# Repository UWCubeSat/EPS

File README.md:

# [Electrical Power System](https://online.huskysatellitelab.com/wiki/index.php/Electrical_Power_System)

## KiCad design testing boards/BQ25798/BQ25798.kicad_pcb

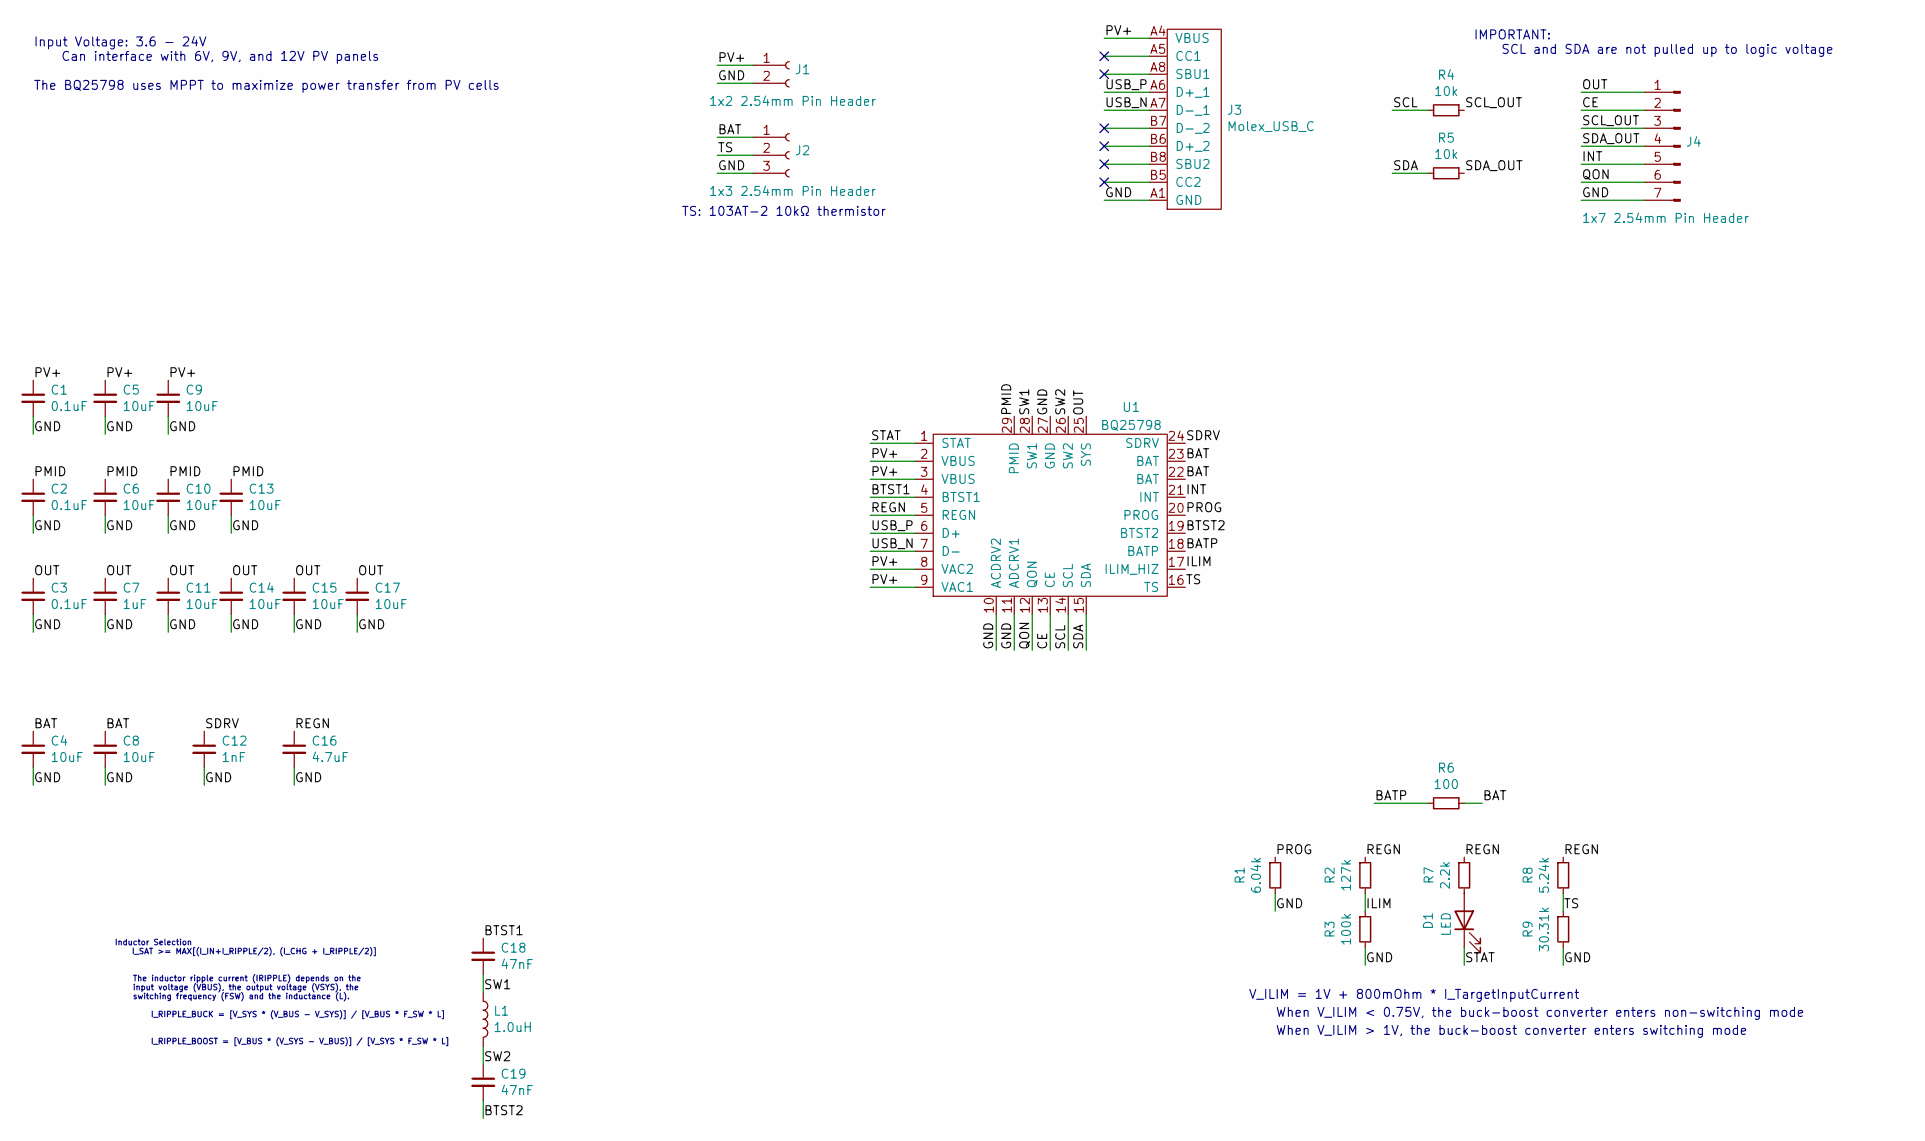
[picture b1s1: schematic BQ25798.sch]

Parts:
C1, C2, C3: 0.1uF; C_0603_1608Metric
C4, C5, C6, C8, C9, C10, C11, C13, C14, C15, C17: 10uF; C_0603_1608Metric
C7: 1uF; C_0603_1608Metric
C12: 1nF; C_0603_1608Metric
C16: 4.7uF; C_0603_1608Metric
C18, C19: 47nF; C_0603_1608Metric
D1: LED; LED_0402_1005Metric
J1: 1x2 2.54mm Pin Header; PinHeader_1x02_P2.54mm_Vertical
J2: 1x3 2.54mm Pin Header; PinHeader_1x03_P2.54mm_Vertical
J3: Molex_USB_C; USB-C
J4: 1x7 2.54mm Pin Header; PinHeader_1x07_P2.54mm_Vertical
L1: 1.0uH; L_0805_2012Metric
R1: 6.04k; R_0402_1005Metric
R2: 127k; R_0402_1005Metric
R3: 100k; R_0402_1005Metric
R4, R5: 10k; R_0402_1005Metric
R6: 100; R_0402_1005Metric
R7: 2.2k; R_0402_1005Metric
R8: 5.24k; R_0402_1005Metric
R9: 30.31k; R_0402_1005Metric
U1: BQ25798

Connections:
/BAT: C4.1, C8.1, J2.1, R6.1, U1.22 (BAT), U1.23 (BAT)
/BATP: R6.2, U1.18 (BATP)
/BTST1: C18.1, U1.4 (BTST1)
/BTST2: C19.2, U1.19 (BTST2)
/CE: J4.2, U1.13 (CE)
/GND: C1.2, C2.2, C3.2, C4.2, C5.2, C6.2, C7.2, C8.2, C9.2, C10.2, C11.2, C12.2, C13.2, C14.2, C15.2, C16.2, C17.2, J1.2, J2.3, J3.A1 (GND), J4.7, R1.2, R3.2, R9.2, U1.10 (ACDRV2), U1.11 (ADCRV1), U1.27 (GND)
/ILIM: R2.2, R3.1, U1.17 (ILIM_HIZ)
/INT: J4.5, U1.21 (INT)
/OUT: C3.1, C7.1, C11.1, C14.1, C15.1, C17.1, J4.1, U1.25 (SYS)
/PMID: C2.1, C6.1, C10.1, C13.1, U1.29 (PMID)
/PROG: R1.1, U1.20 (PROG)
/PV+: C1.1, C5.1, C9.1, J1.1, J3.A4 (VBUS), U1.2 (VBUS), U1.3 (VBUS), U1.8 (VAC2), U1.9 (VAC1)
/QON: J4.6, U1.12 (QON)
/REGN: C16.1, R2.1, R7.1, R8.1, U1.5 (REGN)
/SCL: R4.2, U1.14 (SCL)
/SCL_OUT: J4.3, R4.1
/SDA: R5.2, U1.15 (SDA)
/SDA_OUT: J4.4, R5.1
/SDRV: C12.1, U1.24 (SDRV)
/STAT: D1.1 (K), U1.1 (STAT)
/SW1: C18.2, L1.1, U1.28 (SW1)
/SW2: C19.1, L1.2, U1.26 (SW2)
/TS: J2.2, R8.2, R9.1, U1.16 (TS)
/USB_N: J3.A7 (D-_1), U1.7 (D-)
/USB_P: J3.A6 (D+_1), U1.6 (D+)
unnamed: D1.2 (A), R7.2

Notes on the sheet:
Input Voltage: 3.6 - 24V Can interface with 6V, 9V, and 12V PV panels The BQ25798 uses MPPT to maximize power transfer from PV cells
Inductor Selection I_SAT >= MAX[(I_IN+I_RIPPLE/2), (I_CHG + I_RIPPLE/2)]
I_RIPPLE_BUCK = [V_SYS * (V_BUS - V_SYS)] / [V_BUS * F_SW * L]
I_RIPPLE_BOOST = [V_BUS * (V_SYS - V_BUS)] / [V_SYS * F_SW * L]
The inductor ripple current (IRIPPLE) depends on the input voltage (VBUS), the output voltage (VSYS), the switching frequency (FSW) and the inductance (L).
V_ILIM = 1V + 800mOhm * I_TargetInputCurrent
When V_ILIM < 0.75V, the buck-boost converter enters non-switching mode
When V_ILIM > 1V, the buck-boost converter enters switching mode
IMPORTANT: SCL and SDA are not pulled up to logic voltage
TS: 103AT-2 10kΩ thermistor

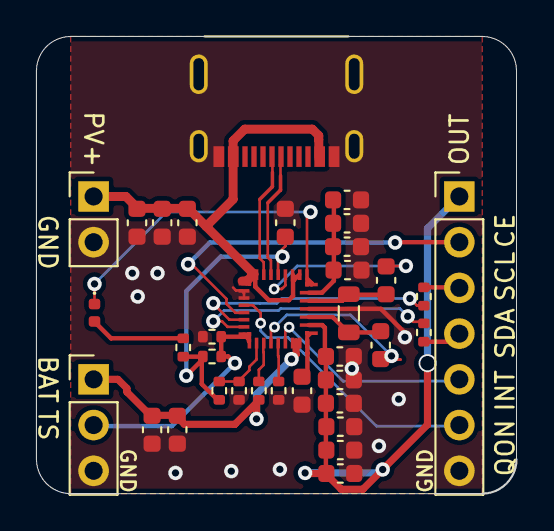
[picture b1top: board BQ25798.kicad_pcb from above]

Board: 2 copper layers, 26.7 x 25.4 mm, 35 parts (0 on the bottom side), 26 nets.

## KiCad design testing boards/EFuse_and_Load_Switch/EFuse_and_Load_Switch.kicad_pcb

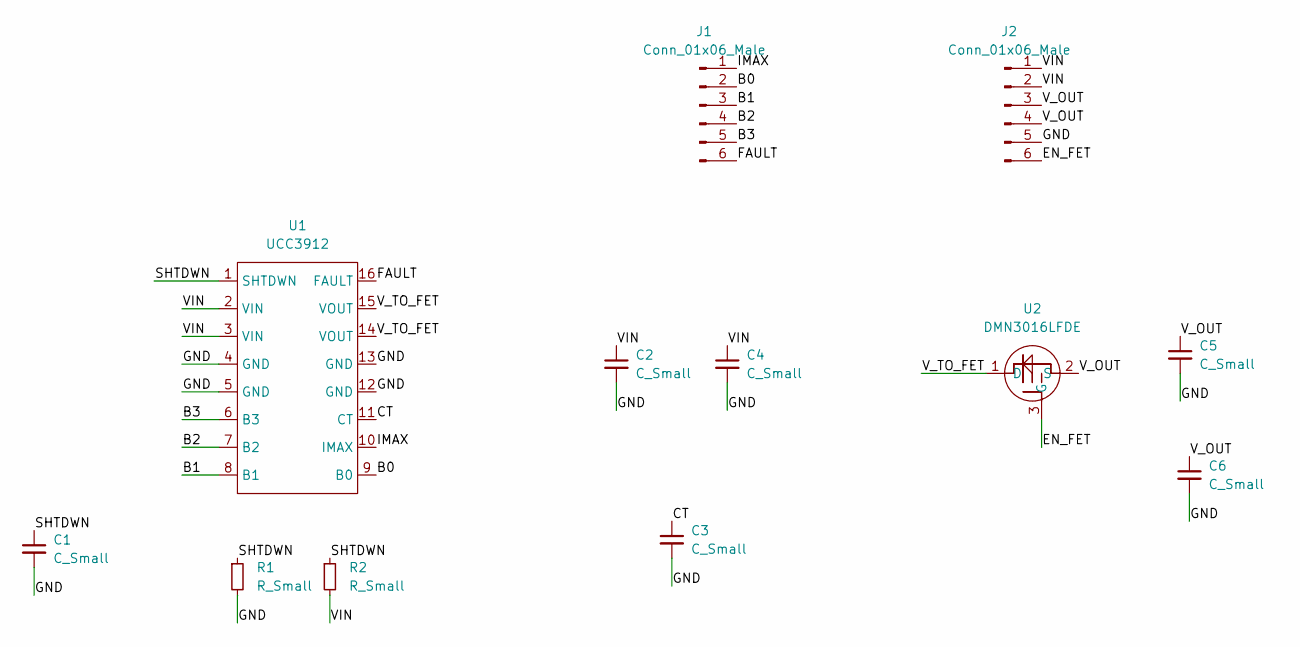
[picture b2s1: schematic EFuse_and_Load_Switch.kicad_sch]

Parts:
C1, C2, C3, C4, C5, C6: C_Small; C_0603_1608Metric
J1, J2: Conn_01x06_Male; PinHeader_1x06_P2.54mm_Vertical
R1, R2: R_Small; R_0402_1005Metric
U1: UCC3912
U2: DMN3016LFDE; U-DFN2020-6

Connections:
/B0: J1.2, U1.9 (B0)
/B1: J1.3, U1.8 (B1)
/B2: J1.4, U1.7 (B2)
/B3: J1.5, U1.6 (B3)
/CT: C3.1, U1.11 (CT)
/EN_FET: J2.6, U2.3 (G)
/FAULT: J1.6, U1.16 (FAULT)
/GND: C1.2, C2.2, C3.2, C4.2, C5.2, C6.2, J2.5, R1.2, U1.4 (GND), U1.5 (GND), U1.12 (GND), U1.13 (GND)
/IMAX: J1.1, U1.10 (IMAX)
/SHTDWN: C1.1, R1.1, R2.1, U1.1 (SHTDWN)
/VIN: C2.1, C4.1, J2.1, J2.2, R2.2, U1.2 (VIN), U1.3 (VIN)
/V_OUT: C5.1, C6.1, J2.3, J2.4, U2.2 (S)
/V_TO_FET: U1.14 (VOUT), U1.15 (VOUT), U2.1 (D)

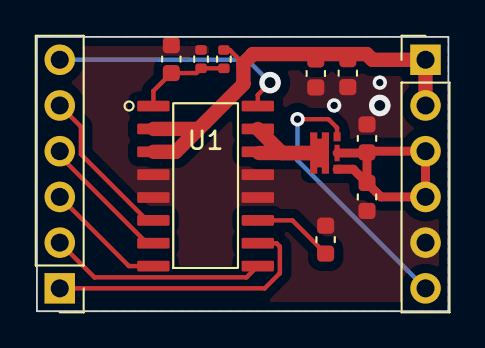
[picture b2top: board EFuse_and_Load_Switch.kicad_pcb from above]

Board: 2 copper layers, 22.9 x 15.2 mm, 12 parts (0 on the bottom side), 13 nets.

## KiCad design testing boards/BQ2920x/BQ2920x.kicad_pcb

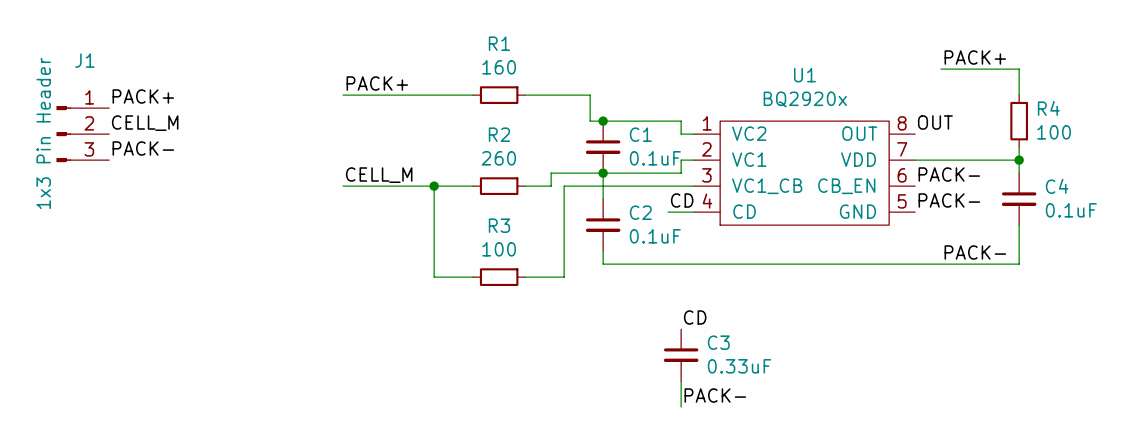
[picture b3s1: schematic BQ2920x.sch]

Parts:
C1, C2, C4: 0.1uF; C_0603_1608Metric
C3: 0.33uF; C_0603_1608Metric
J1: 1x3 Pin Header; PinHeader_1x03_P2.54mm_Vertical
R1: 160; R_0402_1005Metric
R2: 260; R_0402_1005Metric
R3, R4: 100; R_0402_1005Metric
U1: BQ2920x

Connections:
/CD: C3.1, U1.4 (CD)
/CELL_M: J1.2, R2.2, R3.2
/OUT: U1.8 (OUT)
/PACK+: J1.1, R1.2, R4.2
/PACK-: C2.2, C3.2, C4.2, J1.3, U1.5 (GND), U1.6 (CB_EN)
unnamed: C1.1, R1.1, U1.1 (VC2)
unnamed: C1.2, C2.1, R2.1, U1.2 (VC1)
unnamed: C4.1, R4.1, U1.7 (VDD)
unnamed: R3.1, U1.3 (VC1_CB)

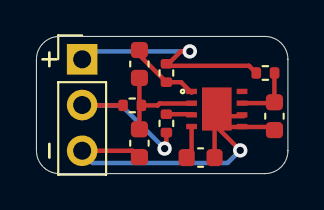
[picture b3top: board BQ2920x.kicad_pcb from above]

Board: 2 copper layers, 14.0 x 7.6 mm, 10 parts (0 on the bottom side), 8 nets.

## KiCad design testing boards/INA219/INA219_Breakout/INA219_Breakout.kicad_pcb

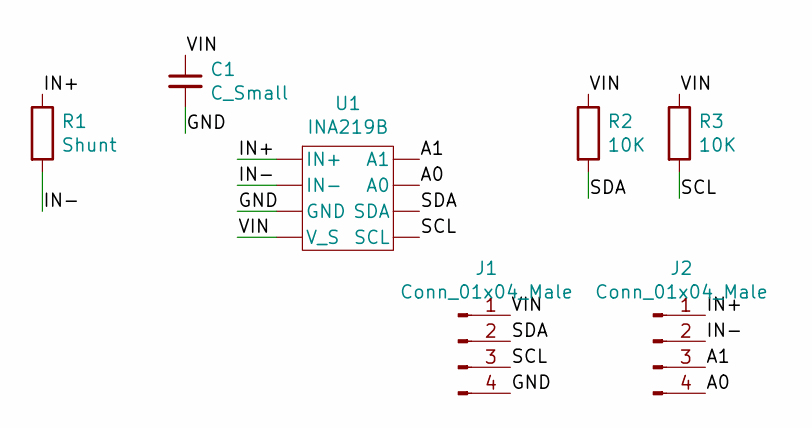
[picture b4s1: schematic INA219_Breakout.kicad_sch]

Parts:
C1: C_Small; C_0603_1608Metric
J1, J2: Conn_01x04_Male; PinHeader_1x04_P2.54mm_Vertical
R1: Shunt; R_2512_6332Metric
R2, R3: 10K; R_0402_1005Metric
U1: INA219B; SOT-23-8

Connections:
/A0: J2.4, U1.7 (A0)
/A1: J2.3, U1.8 (A1)
/GND: C1.2, J1.4, U1.3 (GND)
/IN+: J2.1, R1.1, U1.1 (IN+)
/IN-: J2.2, R1.2, U1.2 (IN-)
/SCL: J1.3, R3.2, U1.5 (SCL)
/SDA: J1.2, R2.2, U1.6 (SDA)
/VIN: C1.1, J1.1, R2.1, R3.1, U1.4 (V_S)

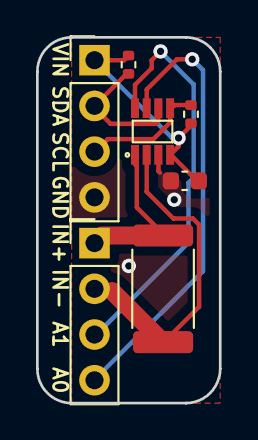
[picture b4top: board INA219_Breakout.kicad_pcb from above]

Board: 2 copper layers, 10.2 x 20.3 mm, 7 parts (0 on the bottom side), 8 nets.

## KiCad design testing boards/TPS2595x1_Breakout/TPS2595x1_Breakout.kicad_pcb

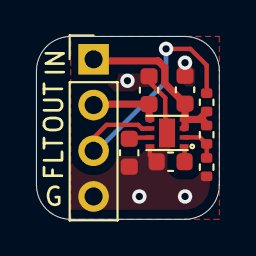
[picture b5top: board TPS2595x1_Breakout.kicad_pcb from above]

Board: 2 copper layers, 10.2 x 10.2 mm, 9 parts (0 on the bottom side), 7 nets.

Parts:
C1, C2, C3, C4: 1uF; C_0603_1608Metric
J1: Pin Header; PinHeader_1x04_P2.54mm_Vertical
R1, R2, R3: 10K; R_0402_1005Metric
U1: TPS2595x1

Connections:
/EN: R1.2, R2.1, U1.2
/FLT: J1.3, R3.2, U1.6
/GND: C1.2, C2.2, C3.2, C4.2, J1.4, R2.2, U1.8
/ILM: C2.1, U1.7
/IN: C3.1, J1.1, R1.1, R3.1, U1.3, U1.4
/OUT: C4.1, J1.2, U1.5
/dVdt: C1.1, U1.1

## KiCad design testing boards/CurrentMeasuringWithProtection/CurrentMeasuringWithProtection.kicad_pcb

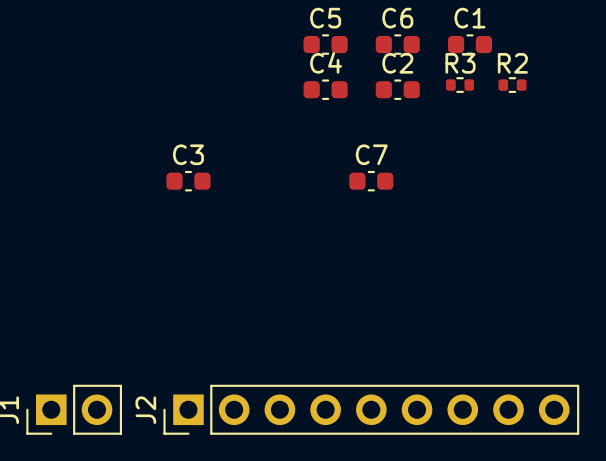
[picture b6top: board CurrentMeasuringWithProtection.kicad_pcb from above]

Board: 2 copper layers, 11 parts (0 on the bottom side), 6 nets, no tracks yet.

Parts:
C1, C2, C3, C4, C5, C6, C7: C_Small; C_0603_1608Metric
J1: Conn_01x02_Male; PinHeader_1x02_P2.54mm_Vertical
J2: Conn_01x09_Male; PinHeader_1x09_P2.54mm_Vertical
R2, R3: R_Small; R_0402_1005Metric

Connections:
/3V3: J2.1, R2.1, R3.1
/GND: C1.2, C2.2, C3.2, C4.2, C5.2, C6.2, C7.2, J2.9
/IN+: C1.1, C2.1, J1.1
/SCL: J2.5, R3.2
/SDA: J2.4, R2.2
/V_OUT: C6.1, C7.1, J1.2

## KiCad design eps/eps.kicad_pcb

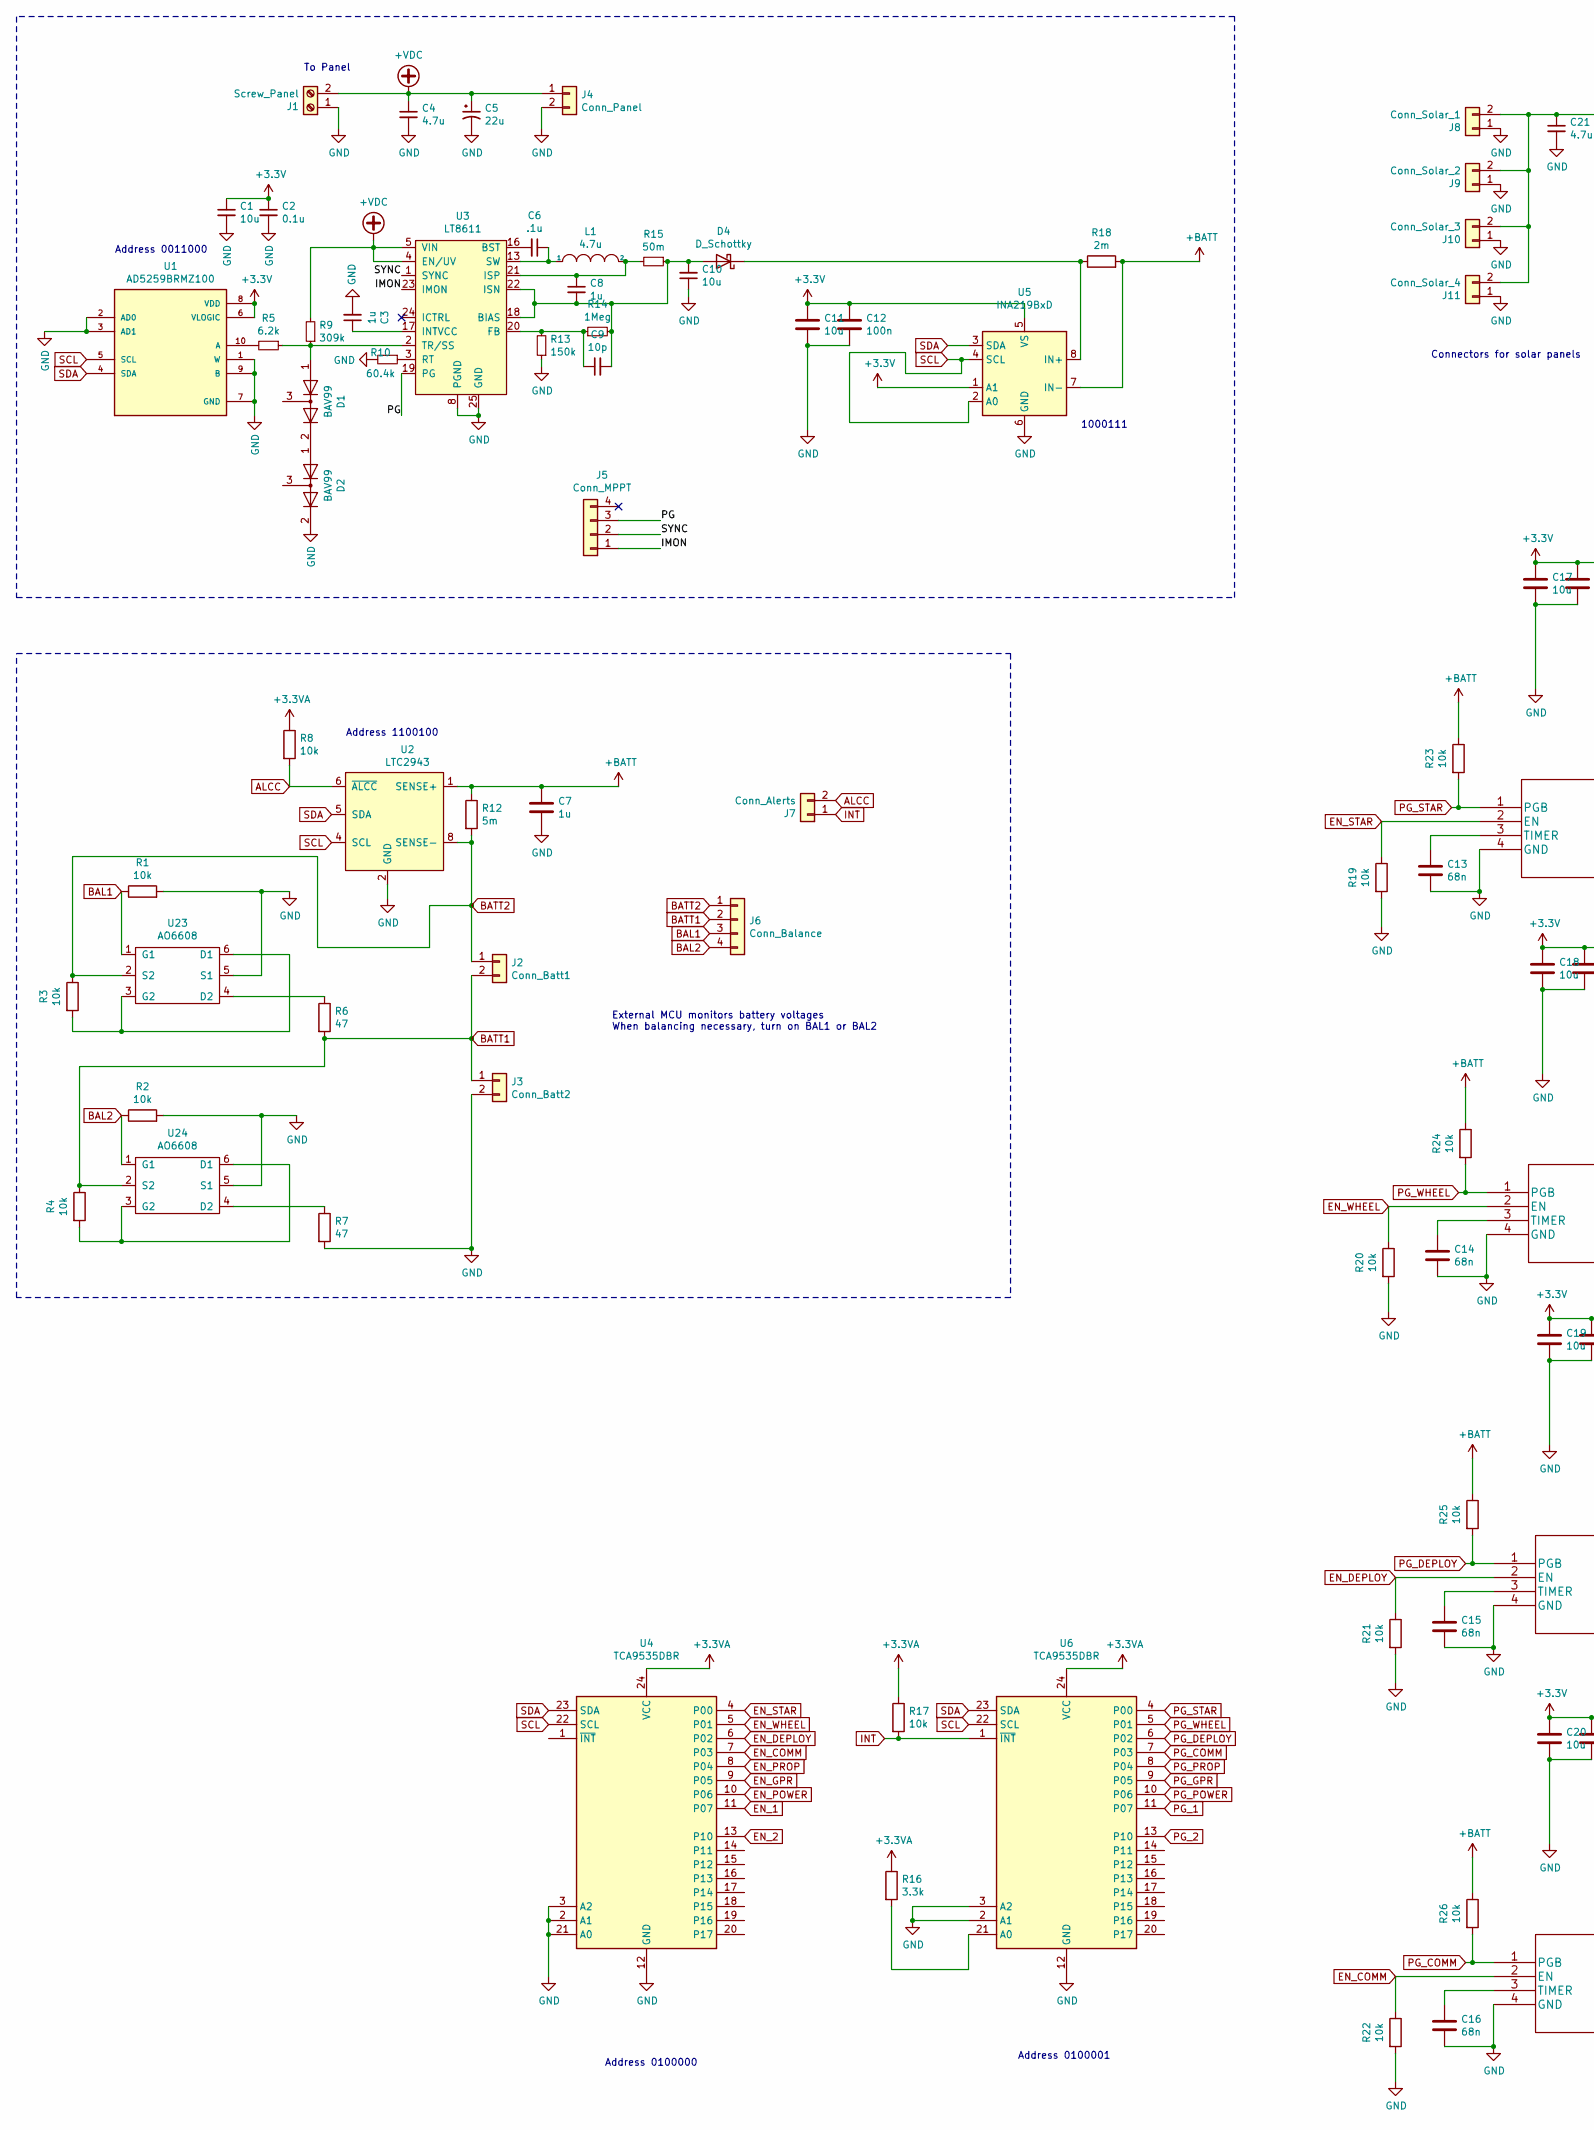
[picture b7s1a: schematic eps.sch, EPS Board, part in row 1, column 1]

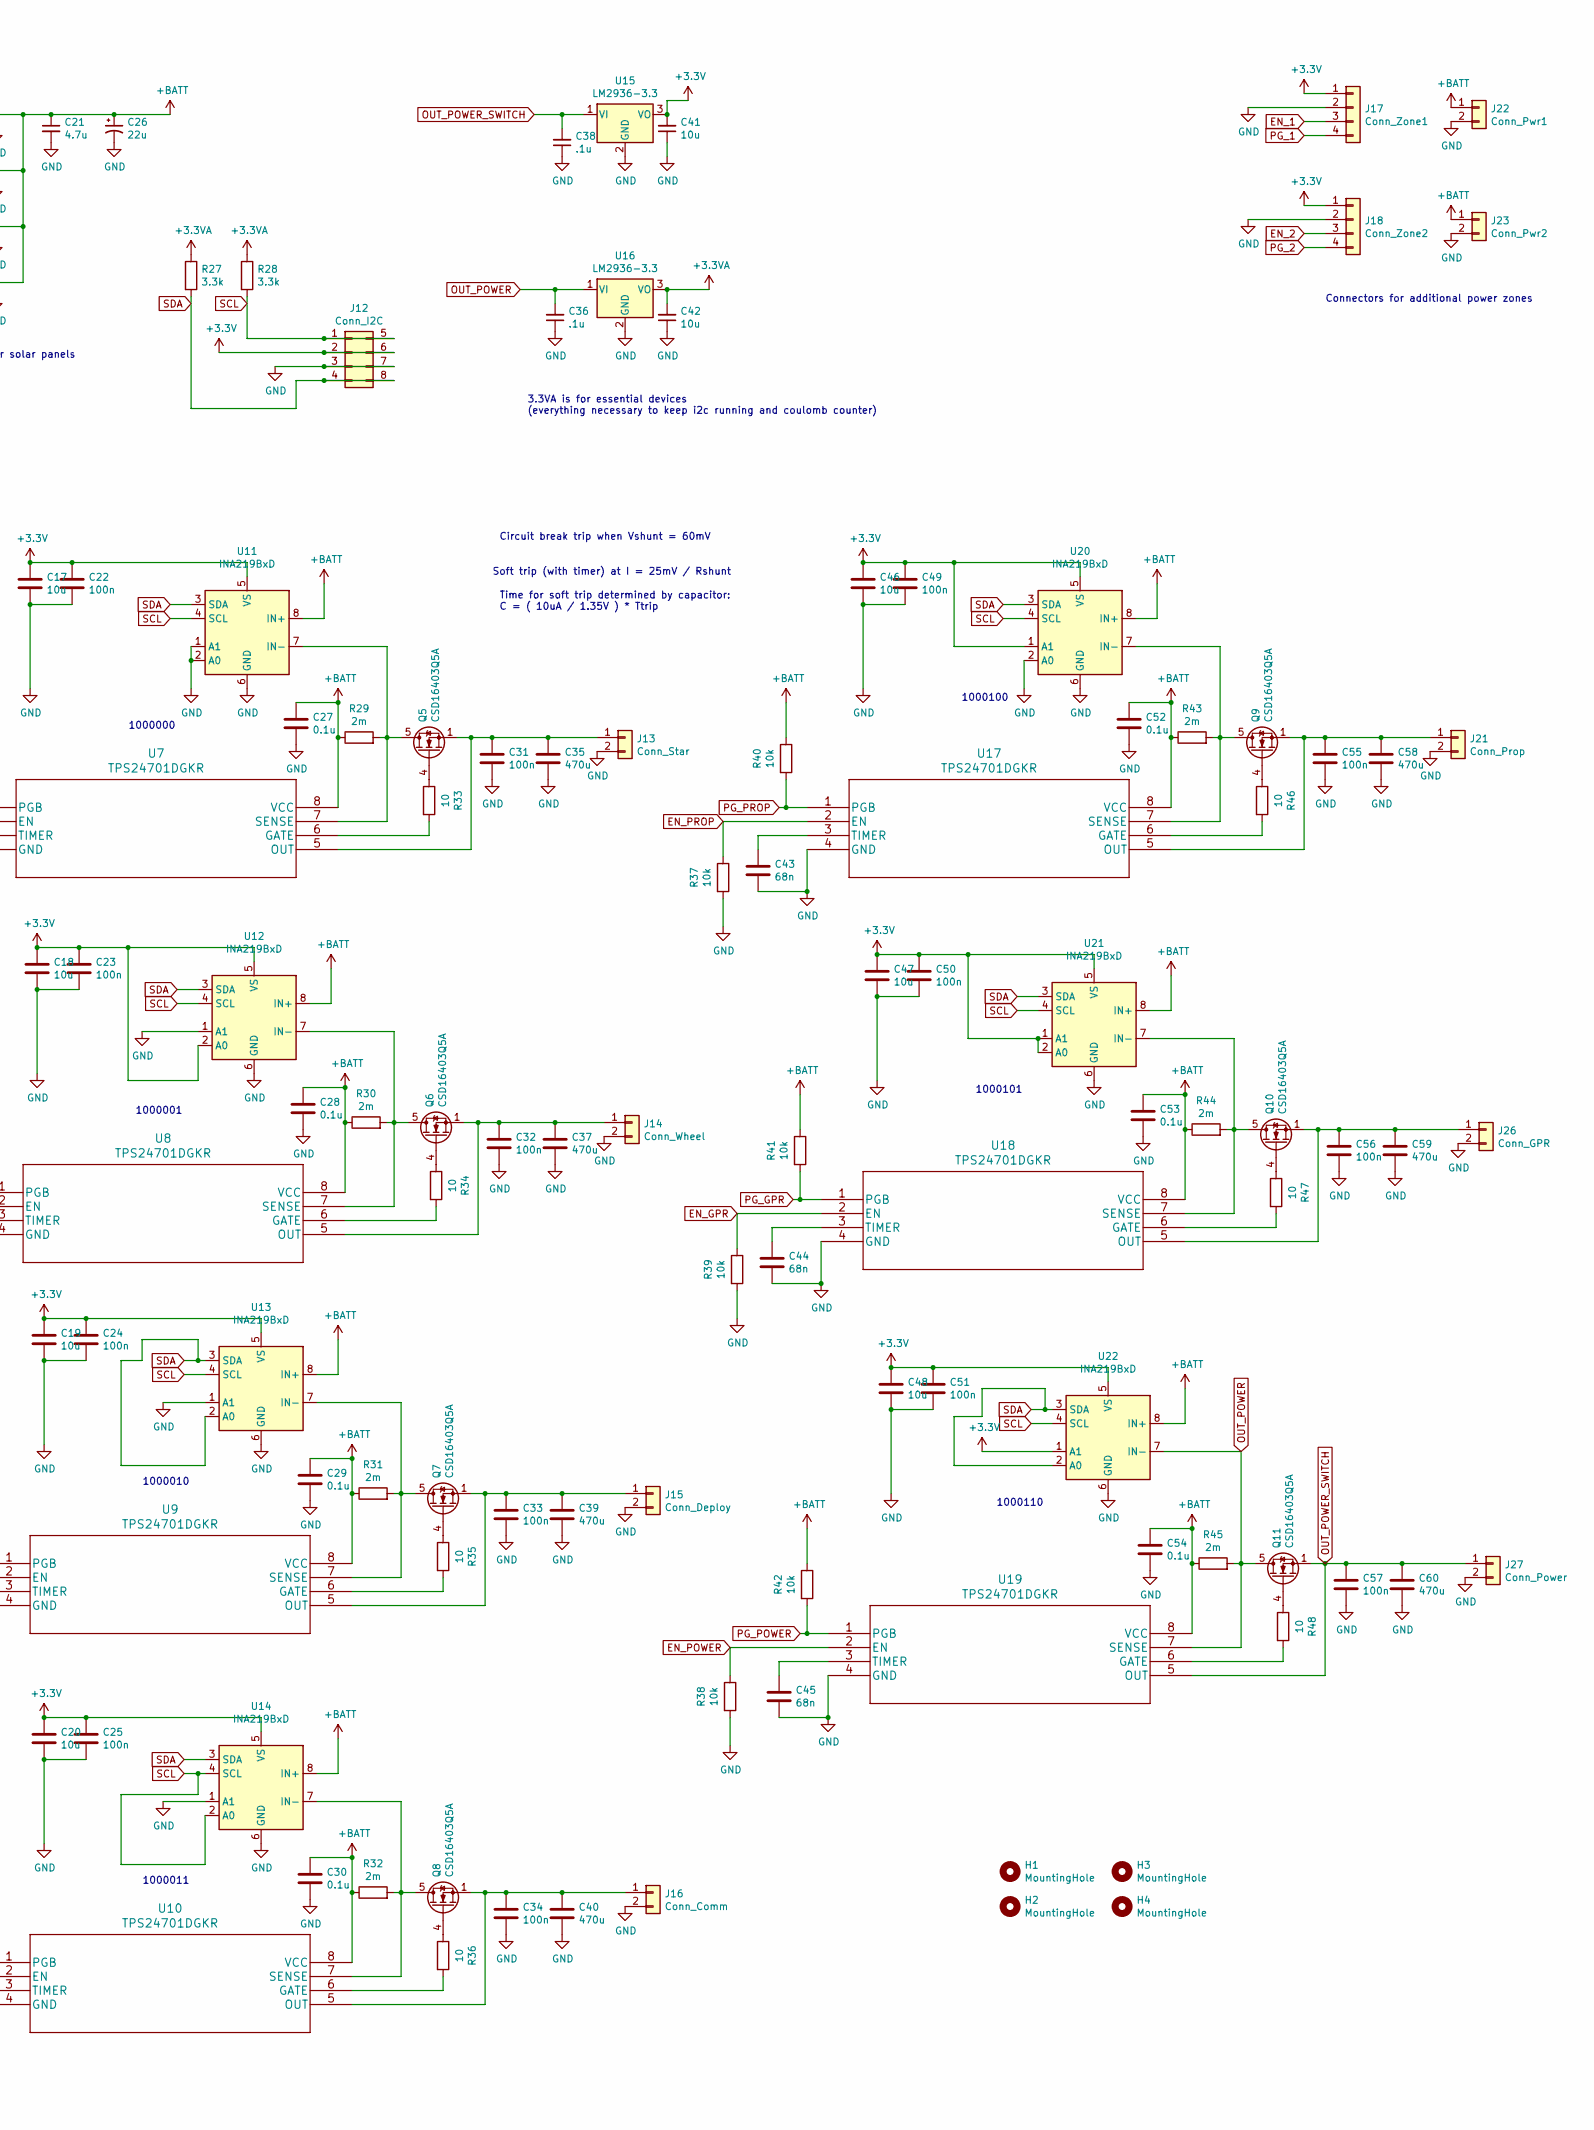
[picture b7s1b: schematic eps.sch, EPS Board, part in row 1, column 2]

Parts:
C1, C10, C11, C17, C18, C19, C20, C41, C42, C46, C47, C48: 10u; C_0805_2012Metric_Pad1.18x1.45mm_HandSolder; Part C15850
C2, C27, C28, C29, C30, C52, C53, C54: 0.1u; C_0805_2012Metric_Pad1.18x1.45mm_HandSolder; Part C49678
C3, C7, C8: 1u; C_0805_2012Metric_Pad1.18x1.45mm_HandSolder; Part C28323
C4, C21: 4.7u; C_0805_2012Metric_Pad1.18x1.45mm_HandSolder; Part C1779
C5, C26: 22u; CP_Radial_D6.3mm_P2.50mm
C6, C36, C38: .1u; C_0805_2012Metric_Pad1.18x1.45mm_HandSolder; Part C49678
C9: 10p; C_0805_2012Metric_Pad1.18x1.45mm_HandSolder; Part C1785
C12, C22, C23, C24, C25, C31, C32, C33, C34, C49, C50, C51, C55, C56, C57: 100n; C_0805_2012Metric_Pad1.18x1.45mm_HandSolder; Part C49678
C13, C14, C15, C16, C43, C44, C45: 68n; C_0805_2012Metric_Pad1.18x1.45mm_HandSolder; Part C1756
C35, C37, C39, C40, C58, C59, C60: 470u; CP_Radial_D8.0mm_P3.50mm
D1, D2: BAV99; SOT-23; Part C2500
D4: D_Schottky; D_SOD-128
H1, H2, H3, H4: MountingHole; MountingHole_2.7mm_M2.5_Pad_Via; Part x
J1: Screw_Panel; TerminalBlock_Phoenix_PT-1,5-2-5.0-H_1x02_P5.00mm_Horizontal
J2: Conn_Batt1; Molex_Micro-Fit_3.0_43045-0212_2x01_P3.00mm_Vertical
J3: Conn_Batt2; Molex_Micro-Fit_3.0_43045-0212_2x01_P3.00mm_Vertical
J4: Conn_Panel; JST_XH_B2B-XH-AM_1x02_P2.50mm_Vertical
J5: Conn_MPPT; JST_XH_B4B-XH-AM_1x04_P2.50mm_Vertical
J6: Conn_Balance; JST_XH_B4B-XH-AM_1x04_P2.50mm_Vertical
J7: Conn_Alerts; JST_XH_B2B-XH-AM_1x02_P2.50mm_Vertical
J8: Conn_Solar_1; JST_XH_B2B-XH-AM_1x02_P2.50mm_Vertical
J9: Conn_Solar_2; JST_XH_B2B-XH-AM_1x02_P2.50mm_Vertical
J10: Conn_Solar_3; JST_XH_B2B-XH-AM_1x02_P2.50mm_Vertical
J11: Conn_Solar_4; JST_XH_B2B-XH-AM_1x02_P2.50mm_Vertical
J12: Conn_I2C; JST_PHD_B8B-PHDSS_2x04_P2.00mm_Vertical
J13: Conn_Star; Molex_Micro-Fit_3.0_43045-0212_2x01_P3.00mm_Vertical
J14: Conn_Wheel; Molex_Micro-Fit_3.0_43045-0212_2x01_P3.00mm_Vertical
J15: Conn_Deploy; Molex_Micro-Fit_3.0_43045-0212_2x01_P3.00mm_Vertical
J16: Conn_Comm; Molex_Micro-Fit_3.0_43045-0212_2x01_P3.00mm_Vertical
J17: Conn_Zone1; JST_XH_B4B-XH-AM_1x04_P2.50mm_Vertical
J18: Conn_Zone2; JST_XH_B4B-XH-AM_1x04_P2.50mm_Vertical
J21: Conn_Prop; Molex_Micro-Fit_3.0_43045-0212_2x01_P3.00mm_Vertical
J22: Conn_Pwr1; Molex_Micro-Fit_3.0_43045-0212_2x01_P3.00mm_Vertical
J23: Conn_Pwr2; Molex_Micro-Fit_3.0_43045-0212_2x01_P3.00mm_Vertical
J26: Conn_GPR; Molex_Micro-Fit_3.0_43045-0212_2x01_P3.00mm_Vertical
J27: Conn_Power; Molex_Micro-Fit_3.0_43045-0212_2x01_P3.00mm_Vertical
L1: 4.7u; BWVS00606045
Q5, Q6, Q7, Q8, Q9, Q10, Q11: CSD16403Q5A; TDSON-8-1
R1, R2, R3, R4, R8, R17, R19, R20, R21, R22, R23, R24, R25, R26, R37, R38, R39, R40, R41, R42: 10k; R_0805_2012Metric_Pad1.20x1.40mm_HandSolder; Part C17414
R5: 6.2k; R_0805_2012Metric_Pad1.20x1.40mm_HandSolder; Part C17767
R6, R7: 47; R_2512_6332Metric_Pad1.40x3.35mm_HandSolder
R9: 309k; R_0805_2012Metric_Pad1.20x1.40mm_HandSolder
R10: 60.4k; R_0805_2012Metric_Pad1.20x1.40mm_HandSolder
R12: 5m; R_2512_6332Metric_Pad1.40x3.35mm_HandSolder
R13: 150k; R_0805_2012Metric_Pad1.20x1.40mm_HandSolder; Part C17470
R14: 1Meg; R_0805_2012Metric_Pad1.20x1.40mm_HandSolder; Part C17514
R15: 50m; R_2512_6332Metric_Pad1.40x3.35mm_HandSolder
R16, R27, R28: 3.3k; R_0805_2012Metric_Pad1.20x1.40mm_HandSolder; Part C26010
R18, R29, R30, R31, R32, R43, R44, R45: 2m; R_0805_2012Metric_Pad1.20x1.40mm_HandSolder
R33, R34, R35, R36, R46, R47, R48: 10; R_0805_2012Metric_Pad1.20x1.40mm_HandSolder; Part C17415
U1: AD5259BRMZ100; SOP50P490X95-10N
U2: LTC2943; DFN-8-1EP_3x3mm_P0.5mm_EP1.66x2.38mm
U3: LT8611; 24-QFN_3x5
U4, U6: TCA9535DBR; SSOP-24_5.3x8.2mm_P0.65mm
U5, U11, U12, U13, U14, U20, U21, U22: INA219BxD; SOIC-8_3.9x4.9mm_P1.27mm
U7, U8, U9, U10, U17, U18, U19: TPS24701DGKR
U15, U16: LM2936-3.3; SOT-223-3_TabPin2
U23, U24: AO6608; SOT-23-6_Handsoldering

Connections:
+3.3VA: C42.2, R8.1, R16.1, R17.1, R27.1, R28.1, U4.24 (VCC), U6.24 (VCC), U16.3 (VO)
+3V3: C1.1, C2.1, C11.1, C12.1, C17.1, C18.1, C19.1, C20.1, C22.1, C23.1, C24.1, C25.1, C41.2, C46.1, C47.1, C48.1, C49.1, C50.1, C51.1, J12.2, J12.6, J17.1, J18.1, U1.6 (VLOGIC), U1.8 (VDD), U5.1 (A1), U5.5 (VS), U11.5 (VS), U12.2 (A0), U12.5 (VS), U13.5 (VS), U14.5 (VS), U15.3 (VO), U20.1 (A1), U20.5 (VS), U21.1 (A1), U21.2 (A0), U21.5 (VS), U22.1 (A1), U22.5 (VS)
+BATT: C7.1, C21.1, C26.1, C27.1, C28.1, C29.1, C30.1, C52.1, C53.1, C54.1, J8.2, J9.2, J10.2, J11.2, J22.1, J23.1, R12.1, R18.2, R23.1, R24.1, R25.1, R26.1, R29.1, R30.1, R31.1, R32.1, R40.1, R41.1, R42.1, R43.1, R44.1, R45.1, U2.1 (SENSE+), U5.7 (IN-), U7.8 (VCC), U8.8 (VCC), U9.8 (VCC), U10.8 (VCC), U11.8 (IN+), U12.8 (IN+), U13.8 (IN+), U14.8 (IN+), U17.8 (VCC), U18.8 (VCC), U19.8 (VCC), U20.8 (IN+), U21.8 (IN+), U22.8 (IN+)
+VDC: C4.1, C5.1, J1.2, J4.1, R9.2, U3.4 (EN/UV), U3.5 (VIN), U3.6 (VIN)
/IMON: J5.1, U3.23 (IMON)
/PG: J5.3, U3.19 (PG)
/SYNC: J5.2, U3.1 (SYNC)
ALCC: J7.2, R8.2, U2.6 (~ALCC~)
BAL1: J6.3, R1.1, U23.1 (G1)
BAL2: J6.4, R2.1, U24.1 (G1)
BATT1: J2.2, J3.1, J6.2, R4.1, R6.2, U24.2 (S2)
BATT2: J2.1, J6.1, R3.1, R12.2, U2.8 (SENSE-), U23.2 (S2)
EN_1: J17.3, U4.11 (P07)
EN_2: J18.3, U4.13 (P10)
EN_COMM: R22.1, U4.7 (P03), U10.2 (EN)
EN_DEPLOY: R21.1, U4.6 (P02), U9.2 (EN)
EN_GPR: R39.1, U4.9 (P05), U18.2 (EN)
EN_POWER: R38.1, U4.10 (P06), U19.2 (EN)
EN_PROP: R37.1, U4.8 (P04), U17.2 (EN)
EN_STAR: R19.1, U4.4 (P00), U7.2 (EN)
EN_WHEEL: R20.1, U4.5 (P01), U8.2 (EN)
GND: C1.2, C2.2, C3.2, C4.2, C5.2, C7.2, C10.1, C11.2, C12.2, C13.2, C14.2, C15.2, C16.2, C17.2, C18.2, C19.2, C20.2, C21.2, C22.2, C23.2, C24.2, C25.2, C26.2, C27.2, C28.2, C29.2, C30.2, C31.2, C32.2, C33.2, C34.2, C35.2, C36.1, C37.2, C38.1, C39.2, C40.2, C41.1, C42.1, C43.2, C44.2, C45.2, C46.2, C47.2, C48.2, C49.2, C50.2, C51.2, C52.2, C53.2, C54.2, C55.2, C56.2, C57.2, C58.2, C59.2, C60.2, D2.2 (A), J1.1, J3.2, J4.2, J8.1, J9.1, J10.1, J11.1, J12.3, J12.7, J13.2, J14.2, J15.2, J16.2, J17.2, J18.2, J21.2, J22.2, J23.2, J26.2, J27.2, R1.2, R2.2, R7.2, R10.2, R13.1, R19.2, R20.2, R21.2, R22.2, R37.2, R38.2, R39.2, U1.1 (W), U1.2 (AD0), U1.3 (AD1), U1.7 (GND), U1.9 (B), U2.2 (GND), U2.3 (NC), U2.7 (NC), U2.9, U3.7 (PGND), U3.8 (PGND), U3.9 (NC), U3.10 (NC), U3.11 (NC), U3.12 (NC), U3.25 (GND), U4.2 (A1), U4.3 (A2), U4.12 (GND), U4.21 (A0), U5.6 (GND), U6.2 (A1), U6.3 (A2), U6.12 (GND), U7.4 (GND), U8.4 (GND), U9.4 (GND), U10.4 (GND), U11.1 (A1), U11.2 (A0), U11.6 (GND), U12.1 (A1), U12.6 (GND), U13.1 (A1), U13.6 (GND), U14.1 (A1), U14.6 (GND), U15.2 (GND), U16.2 (GND), U17.4 (GND), U18.4 (GND), U19.4 (GND), U20.2 (A0), U20.6 (GND), U21.6 (GND), U22.6 (GND), U23.5 (S1), U24.5 (S1)
INT: J7.1, R17.2, U6.1 (~INT)
unnamed: C3.1, U3.17 (INTVCC)
unnamed: C6.1, L1.1, U3.13 (SW), U3.14 (SW), U3.15 (SW)
unnamed: C6.2, U3.16 (BST)
unnamed: C8.1, L1.2, R15.2, U3.21 (ISP)
unnamed: C9.1, R13.2, R14.1, U3.20 (FB)
unnamed: C8.2, C9.2, C10.2, D4.2 (A), R14.2, R15.1, U3.18 (BIAS), U3.22 (ISN)
unnamed: C13.1, U7.3 (TIMER)
unnamed: C14.1, U8.3 (TIMER)
unnamed: C15.1, U9.3 (TIMER)
unnamed: C16.1, U10.3 (TIMER)
unnamed: C31.1, C35.1, J13.1, Q5.1 (S), Q5.2 (S), Q5.3 (S), U7.5 (OUT)
unnamed: C32.1, C37.1, J14.1, Q6.1 (S), Q6.2 (S), Q6.3 (S), U8.5 (OUT)
unnamed: C33.1, C39.1, J15.1, Q7.1 (S), Q7.2 (S), Q7.3 (S), U9.5 (OUT)
unnamed: C34.1, C40.1, J16.1, Q8.1 (S), Q8.2 (S), Q8.3 (S), U10.5 (OUT)
unnamed: C43.1, U17.3 (TIMER)
unnamed: C44.1, U18.3 (TIMER)
unnamed: C45.1, U19.3 (TIMER)
unnamed: C55.1, C58.1, J21.1, Q9.1 (S), Q9.2 (S), Q9.3 (S), U17.5 (OUT)
unnamed: C56.1, C59.1, J26.1, Q10.1 (S), Q10.2 (S), Q10.3 (S), U18.5 (OUT)
unnamed: D1.1 (K), R5.1, R9.1, U3.2 (TR/SS)
unnamed: D1.2 (A), D2.1 (K)
unnamed: D4.1 (K), R18.1, U5.8 (IN+)
unnamed: Q5.4 (G), R33.1
unnamed: Q5.5 (D), R29.2, U7.7 (SENSE), U11.7 (IN-)
unnamed: Q6.4 (G), R34.1
unnamed: Q6.5 (D), R30.2, U8.7 (SENSE), U12.7 (IN-)
unnamed: Q7.4 (G), R35.1
unnamed: Q7.5 (D), R31.2, U9.7 (SENSE), U13.7 (IN-)
unnamed: Q8.4 (G), R36.1
unnamed: Q8.5 (D), R32.2, U10.7 (SENSE), U14.7 (IN-)
unnamed: Q9.4 (G), R46.1
unnamed: Q9.5 (D), R43.2, U17.7 (SENSE), U20.7 (IN-)
unnamed: Q10.4 (G), R47.1
unnamed: Q10.5 (D), R44.2, U18.7 (SENSE), U21.7 (IN-)
unnamed: Q11.4 (G), R48.1
unnamed: R3.2, U23.3 (G2), U23.6 (D1)
unnamed: R4.2, U24.3 (G2), U24.6 (D1)
unnamed: R5.2, U1.10 (A)
unnamed: R6.1, U23.4 (D2)
unnamed: R7.1, U24.4 (D2)
unnamed: R10.1, U3.3 (RT)
unnamed: R16.2, U6.21 (A0)
unnamed: R33.2, U7.6 (GATE)
unnamed: R34.2, U8.6 (GATE)
unnamed: R35.2, U9.6 (GATE)
unnamed: R36.2, U10.6 (GATE)
unnamed: R46.2, U17.6 (GATE)
unnamed: R47.2, U18.6 (GATE)
unnamed: R48.2, U19.6 (GATE)
OUT_POWER: C36.2, Q11.5 (D), R45.2, U16.1 (VI), U19.7 (SENSE), U22.7 (IN-)
OUT_POWER_SWITCH: C38.2, C57.1, C60.1, J27.1, Q11.1 (S), Q11.2 (S), Q11.3 (S), U15.1 (VI), U19.5 (OUT)
PG_1: J17.4, U6.11 (P07)
PG_2: J18.4, U6.13 (P10)
PG_COMM: R26.2, U6.7 (P03), U10.1 (PGB)
PG_DEPLOY: R25.2, U6.6 (P02), U9.1 (PGB)
PG_GPR: R41.2, U6.9 (P05), U18.1 (PGB)
PG_POWER: R42.2, U6.10 (P06), U19.1 (PGB)
PG_PROP: R40.2, U6.8 (P04), U17.1 (PGB)
PG_STAR: R23.2, U6.4 (P00), U7.1 (PGB)
PG_WHEEL: R24.2, U6.5 (P01), U8.1 (PGB)
SCL: J12.1, J12.5, R28.2, U1.5 (SCL), U2.4 (SCL), U4.22 (SCL), U5.2 (A0), U5.4 (SCL), U6.22 (SCL), U11.4 (SCL), U12.4 (SCL), U13.4 (SCL), U14.2 (A0), U14.4 (SCL), U20.4 (SCL), U21.4 (SCL), U22.4 (SCL)
SDA: J12.4, J12.8, R27.2, U1.4 (SDA), U2.5 (SDA), U4.23 (SDA), U5.3 (SDA), U6.23 (SDA), U11.3 (SDA), U12.3 (SDA), U13.2 (A0), U13.3 (SDA), U14.3 (SDA), U20.3 (SDA), U21.3 (SDA), U22.2 (A0), U22.3 (SDA)

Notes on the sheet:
3.3VA is for essential devices (everything necessary to keep i2c running and coulomb counter)
Address 0100000
1000101
1000110
1000100
1000011
1000010
1000000
1000001
Address 0100001
Connectors for additional power zones
Connectors for solar panels
Circuit break trip when Vshunt = 60mV
Soft trip (with timer) at I = 25mV / Rshunt
Time for soft trip determined by capacitor: C = ( 10uA / 1.35V ) * Ttrip
Address 1100100
External MCU monitors battery voltages When balancing necessary, turn on BAL1 or BAL2
To Panel
Address 0011000
1000111

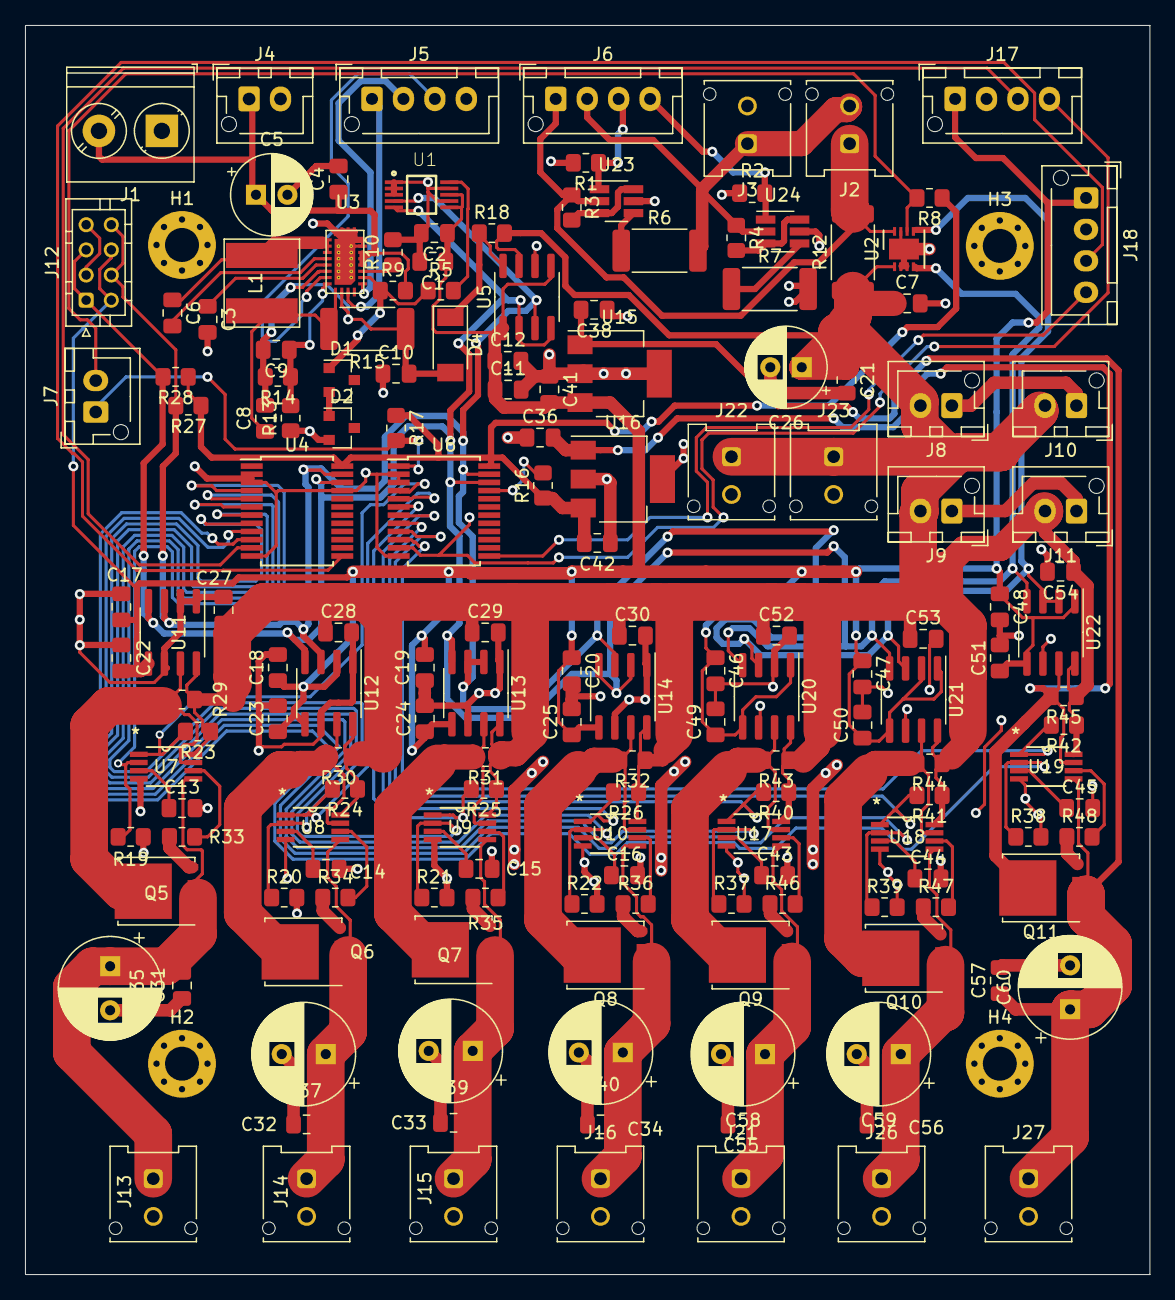
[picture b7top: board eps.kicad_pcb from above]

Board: 2 copper layers, 89.4 x 99.3 mm, 169 parts (0 on the bottom side), 85 nets.

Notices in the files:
parts and their libraries:
Copyright 2016 Accelerated Designs. All rights reserved.
